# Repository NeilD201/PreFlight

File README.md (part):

# PCB Preflight — circuit review and manufacturing handoff

_Preflight was completely built during the hackathon — none of it was started before the hackathon kickoff._

> 🎬 **Hackathon demo video:** _link coming soon — placeholder for the recorded
> walkthrough (wrong board → findings → SRV05-4 prescription → disposable fix)._

Read a KiCad project folder or ZIP, compare schematic and PCB components and
connections, run KiCad's electrical and board rule checks, explain their practical
significance, and optionally ask AI to review the structured evidence. Requires
Python 3.10 or newer. The local checks use the standard library; PDF reading uses pypdf.
KiCad 9+ supplies the optional netlist/ERC/DRC engine (tested with KiCad 9.0.5).
See [project structure and data flow](docs/PROJECT_STRUCTURE.md) for a source
map, outbound service list, and local-data notes before publishing or sharing.
Two bundled demo boards (`demo-projects/ModularKeyboard wrong` and
`demo-projects/ModularKeyboard correct`) open with one click from the Projects
page — no upload needed. Both boards are the developer's WenneBoard project:
[wrong-board context](demo-projects/ModularKeyboard%20wrong/preset-context.md)
and [correct-board context](demo-projects/ModularKeyboard%20correct/preset-context.md)
(full text in [DEMO_GUIDE.md](DEMO_GUIDE.md)). After opening a demo and
running an analysis, load it via **Project context → Load preset → Save
context** so Vector can use the detailed WenneBoard information in
future reviews.

## Quick Start for Judges (under two minutes)

1. **Install:** Python 3.10+ (python.org, or `py -3` on Windows), then in the
   cloned folder create and activate a venv (exact PowerShell vs Command
   Prompt commands in SETUP.md §3), then `pip install -r requirements.txt`.
   Optional but recommended: KiCad 9+ (kicad.org) for native ERC/DRC and
   manufacturing checks — without it those checks report NOT PERFORMED
   instead of guessing.
2. **Launch:** `python main.py --web` and open the printed URL.
3. **API key (only needed for AI answers):** get a Meta API key with Muse
   Spark 1.3 Contributor access, then paste it in **Vector settings → Save &
   test**, or put `LLAMA_API_KEY=your-key` in an untracked `.env` file
   (see `.env.example`). Without a key, all local checks, findings, and
   previews still work; AI review and Vector answers report unavailable.
4. **Demo:** open **ModularKeyboard Wrong**, press **Check my board**, inspect
   the C105 capacitor and LED-resistor findings (USB-C CC detail and Vector
   follow-ups need the key), then open **ModularKeyboard Correct** to
   compare. See the full walkthrough below.

## What PreFlight is (and is not)

PreFlight reviews an **existing PCB design before manufacturing**: it reads your
KiCad schematic and PCB, checks that they agree, runs the electrical and
manufacturing rules that matter for a working board, and explains each finding
with evidence you can inspect. It was built because raw DRC output tells you
*what* violates a rule but not *whether it matters* — and because generic AI
chat answers printed-circuit questions without ever reading the design files.

PreFlight is **not an AI PCB generator** and does not lay out boards. Deterministic
checks (parsing, connectivity, ERC/DRC, manufacturing rules) always run locally
and are free. Meta Muse Spark is used only as a reasoning assistant over that
evidence — citations required, nothing accepted on a model's word alone.

## Judge walkthrough (about 10 minutes, no API key needed for steps 1–5)

1. Install and launch: `python3 -m venv .venv && source .venv/bin/activate`
   (Windows: `py -3 -m venv .venv`), `pip install -r requirements.txt`,
   then `python main.py --web` and open the printed URL.
2. On the Projects page, open **ModularKeyboard Wrong** (display name for the
   bundled `ModularKeyboard wrong` demo). It opens as a disposable working
   copy — the bundled originals are never modified.
3. Press **Check my board**. The local analysis runs on your machine (tens of
   seconds) with no API key.
4. Open **R001 — 100 µF capacitor (C105)**: rails (+5V, +3.3V), regulators,
   and every powered load pin, with steps naming exactly what is unverified.
   Open **R005 — LED series resistance (R12–R14)** for the screening
   estimate. (The USB-C CC pull-down detail appears with a Meta key's
   Vector review, not in the free local pass.)
5. Open a finding: schematic/PCB evidence, the pins and nets involved, and
   what would need to change. With a Meta key configured, ask Vector a
   follow-up (e.g. why the value matters); without a key this step reports
   itself as unavailable instead of guessing.
6. Open **ModularKeyboard Correct** and compare: the same checks pass there.
7. Explore the other findings (regulator pads, copper clearance, ESD
   protection) and the board preview, schematic view, and manufacturing
   checks.

A full AI review of a 400+-part board takes several minutes and a few cents of
Meta credit; nothing in the walkthrough above requires it.

## Reading a verdict: PASS, FAIL, NOT VERIFIED, NOT PERFORMED

- **Supported / fixed:** a deterministic check ran and the evidence meets the
  requirement, or a repair was applied to a disposable copy and re-verified.
- **FAIL / finding:** a check ran and the evidence contradicts the requirement.
  Each finding cites components, nets, pins, and source evidence.
- **NOT VERIFIED:** the evidence is incomplete, contradictory, or needs a
  measurement, simulation, or answer only you can give. Nothing is declared
  safe on missing evidence.
- **NOT PERFORMED / unavailable:** a check could not run (for example KiCad or
  datasheet PDFs are missing, or no Meta key is configured). The report says
  so instead of passing silently.

PreFlight never invents a specification, never treats an AI opinion as proof
on its own, and never edits your original KiCad files — repairs apply to
disposable copies only.

## Keep AI usage low

For a model-directed engineering investigation, choose **Vector settings → Vector
usage → Vector investigation · detailed review**. Vector selects evidence tools,
reviews their results, retrieves additional passages for open questions, and
challenges its circuit conclusions. The saved review includes an expandable
execution record. It shares the existing 12-request allowance. See [Vector
pipeline](docs/VECTOR_PIPELINE.md) for capabilities,
repair validation, and limits.

If a saved review has an AI failure, use **Retry AI review** on Overview or in
**More tools → Review log**. This reviews the saved board with the latest saved
product context. It reuses local checks, datasheets, assembly results and previews;
it does not rerun KiCad or look up the same parts again. Changed linked KiCad files
require **Update review** first. Repeated clicks do not start duplicate requests.
The result is saved as a new review, preserving the previous report.

**Save & test** sends one small structured request, with no PCB data. A successful
connection test establishes that the selected key and model answered that test;
the board review still needs to complete. Request limits do not replace the
provider's actual error, and incomplete responses never become accepted edits.

After reading the project, **Tell PreFlight about your project** invites one free-text
description of what you are building (up to 6,000 characters, saved with **Save &
analyse**). The description enters the engineering evidence and the optional Vector
review; it can be edited later. **Questions from your files** then asks only about
missing external facts identified from components and pin/net connections. For example, a charger
prompts for its attached battery, and a radio prompts for its final enclosure.
Each question shows what the files already establish. Questions are generated
locally for recognized circuit patterns, with no AI requests; they do not cover
every possible missing requirement. The AI review waits for these answers.
Choose **Not sure yet** when needed. **Product details** lets you revise answers.
Every **Continue** saves the answer immediately to `reports/.preflight.sqlite3`,
including **Not sure yet**. Closing the questionnaire or failing an AI request
does not discard submitted answers. Only unanswered questions are queued; completed
interviews open their saved-answer summary. Product-use answers survive board edits;
component-specific answers require reconfirmation when their electrical basis changes.
Reviews, chat and repair planning receive the question text alongside
these assumptions and related edge cases. Unknowns do not become passed checks.
Closing the questions preserves local results and leaves the AI review pending.
**Questions & saved answers** also lets you save AI follow-up answers without
starting a paid review. Repair answers are saved before the next investigation.
Context revisions are journaled in SQLite, and stale writes from another tab are
rejected rather than overwriting newer answers.

PreFlight uses one complete-investigation tier: there is no economy mode.
A Vector review uses up to 12 provider requests, including evidence-tool
investigations, per-finding verification, and a bounded repair loop. Repair
actions have their own per-action request cap; chat answers have a 2-request
cap. Each click that starts a new action gets a new allowance. These are
request limits, **not a euro spending cap**; token usage depends on the
project and response length. Local validation still runs, and unresolved
checks or unsafe edits are not accepted to fit any allowance.

Identical, fully validated reviews are reused in memory for up to 30 minutes
(eight entries maximum). Changed evidence, source hashes, context, model or
credentials require a fresh review. Partial or failed reviews are not reused.
Opening the app and saving settings do not test the API. **Save & test** sends
one small paid request. The AI review panel shows requests sent for new reviews.

## Start the browser app

From the project folder (whatever it is named), run:

```sh
python3 launch_app.py
```

This opens **http://127.0.0.1:8765** and keeps the app running in the background.
You can close the launch window. Double-click **Start PCB Preflight.command** in
the project folder to start it again; if it is already running, this reopens it.
Startup details are saved in `reports/.webserver.log`. For a foreground server
that stops with Ctrl+C, use `python3 main.py --web`.
Connect the `.kicad_pro`, `.kicad_sch` and `.kicad_pcb` files you edit in KiCad.
Save in KiCad, then click **Update** to read the saved files again. You can also
use **Upload ZIP** to check a KiCad archive (up to 100 MiB).

**Overview** lists active issues first, with **View issue**, **Fix this issue**, and
**Ask about it**. **Chat** beside **Review** is a general conversation: ask anything,
with no required issue or step. It uses a compact snapshot of the open project and
relevant saved evidence automatically, and also works without a project. Opening it
sends no AI request. Each message uses the existing two-request chat allowance, without
rerunning the review. Project conversations are stored in SQLite and restored across
updates and restarts. **Clear chat view** clears the visible conversation while
keeping saved history. The latest 100 exchanges are visible; the full archive remains
in the database. Up to 20 recent user messages with their preceding prompts, bounded
to 12 KB, are supplied as conversational context. Explicit product and follow-up
answers are supplied separately. Assistant suggestions are not saved as verified facts.
Chats without an open project remain session-only. Issue-specific
help remains available inside each issue. The repair
workflow prepares and checks proposed changes before approval; the button does not
mean every finding has an automatic edit. The manufacturing checklist follows. It separates
completed checks, findings to review and unverified engineering requirements.
It covers connections, power, PCB geometry, signals, mechanical fit, parts,
test access and production files. Expand a section for its evidence and next action.

New full runs refill copper on a temporary copy using KiCad Python, run DRC and
schematic parity, then export Gerber and Excellon drill drafts from that same copy.
The app validates layer attributes (including renamed copper layers), includes
source and output SHA-256 hashes, and offers the checked PCB copy for inspection.
Analysis leaves the original project unchanged. Missing KiCad Python, invalid outlines and
export failures remain visible; they never produce a fabricated success result.

### Optional file fixes

Each finding has **Fix this issue** above **Observation**, beside the design preview.
The details follow **Observation → Action → Consequence**, with supporting analysis below.
The button opens the available fix options for that finding.
For supported edits, save and close that board’s PCB Editor window,
tick the confirmation, then click **Apply fix**. The project manager and schematic can stay open. The app
prepares a copy, validates the edit, keeps a backup, and applies it automatically
if the checks pass. It currently supports copying one mismatched PCB Value field
from its matching schematic symbol, and short ground connections (up to 1.5 mm)
between an identified pad and a straight track on the same copper layer/net.
For other findings, **Fix this issue** starts an investigation in that same window when Meta is connected.
Progress, the repair assessment, retries and follow-up questions stay there. Closing and reopening
the window during the same page session keeps the investigation; it does not send it again.
Investigation requests retry transient server/connection failures up to three attempts, with
a 45-second socket timeout per attempt and a shared 120-second retry budget. Authentication,
quota, certificate and permanent DNS failures are reported without automatic retries.
The investigation asks Meta Muse Spark to assess whether a change
is needed using the selected path, connected parts, stored design context and available
datasheet excerpts. KiCad can stay open during this assessment. Chat proposes changes;
it cannot write files. Other edits remain manual.

Copper proposals must remove the exact unconnected-items finding after a KiCad
refill and DRC comparison without introducing new non-excluded DRC findings.
These checks use the saved rules and do not validate return-current behavior or EMI.
Keep the PCB Editor closed while the fix runs. The app checks source hashes again, keeps an original
backup, and replaces only the selected PCB file. Reopen the PCB in KiCad and
update the review using the button in the completion message. **Undo this fix** restores the original only if no subsequent
PCB edits would be overwritten. Previews and backups are in `reports/.file-fixes/`.
Edits require a connected local folder; uploaded files and ZIPs are copies.

The checklist also exposes ignored rules and saved exceptions. Symbol pin names
can identify I²C lines even when nets have arbitrary names; fitted pull-ups are
traced to recognized supplies and parallel resistance is calculated. Supply
voltages, bus timing, addresses and alternate pin functions still require evidence.
See [the manufacturing check coverage](docs/PREMANUFACTURING.md) for scope.

The top menu has three review sections:

- **Circuit**: supported circuit concerns from pin requirements, datasheet passages,
  functional paths and operating context. Raw ERC does not become a connection mistake
  on its own. Pin analysis can raise a wiring correction or a specific missing-mode question.
- **PCB layout**: spacing, holes, mask, footprints and assembly checks. These use
  saved KiCad rules; they are not a complete datasheet placement or manufacturing review.
- **Signals**: shorts/unconnected items, circuit paths, radio/sensor routing
  observations, saved stackup, and limited DC trace estimates.

**KiCad & library notes** retains raw ERC, naming, library and unavailable-check notices.
Each section shows a marked preview beside the selected finding, its possible impact
and the next step. Additional steps, analysis and source evidence expand on demand.
The question box stays open for the selected finding; **Ask a question** at the top
jumps to it. You can ask about a footprint note as well as an active issue.
Default-clearance warnings between known pads in the same footprint, and shared mask
openings inside that footprint, are kept in **KiCad & library notes**. They do not
generate pad-moving instructions. This classification does not approve a land pattern
or manufacturing process: shorts, zero gaps, unknown pad ownership, routed tracks and
explicit clearance rules are not suppressed. Old saved AI steps are also corrected
when viewed, without marking these findings fixed or rewriting historical reports.
**Project → Edit intended use & operating details** provides interfaces, power, antenna
and manufacturing fields used together by the AI. Connected files and check settings
also live under **Project**. Empty sections do not certify the design. **More** retains
datasheets, original findings, AI status and the net browser; **BOM & parts** holds exports.

The DC model uses the saved copper thickness and TI's nominal 25 °C resistivity formula.
Only a connected, unbranched, single-layer chain of straight tracks is estimated. Nets
with vias, pours, arcs, branches, loops or intersections remain uncalculated. The estimate
is between drawn track endpoints, not component pins: pads, contacts, parts and heating
are excluded. It is not RF impedance. No return-plane, noise, crosstalk, antenna or thermal
simulation has run, and no acceptable voltage-drop/current limit is inferred.

**Projects** has searchable,
paginated history, including reports previously generated from Terminal. Give each
board a project name and reuse it for later revisions. The last opened run is restored
when the app restarts. Checks use temporary copies of the KiCad files.

### Follow the circuit

**Circuit / Signals → Explore circuit paths** traces the saved schematic connections through
supported charger and regulator stages, fitted series parts, and receiving pins.
Choose a circuit path and, where available, its source route. Click a pin to mark its
saved schematic position, or show the complete path and switch to **PCB** to highlight
its drawn copper. Signal paths also show the shared bus endpoints and side branches.

The smartwatch example includes J1 → U8 → U4, J4 → U4, U4 → U12,
the SCL/SDA sensor buses, and U13 → L1 with the antenna capacitor branches.
The AI review and step helper receive these traced paths alongside pins and datasheet
passages. Unknown internal IC connections and switch states are left unresolved.
A path through a regulator describes its intended function; it does not mean its input
and output share copper. Shunt capacitors are kept separate from DC power paths.
The highlights show saved routing, without calculating noise or impedance.

### Describe the device, then revise the change plan

**Project → What the app understands** describes the device inferred from the selected components.
Without AI this is labelled as an initial interpretation from component names. With
Meta Muse Spark it is reconsidered against the circuit evidence and your stated intent.

1. Correct the description or add constraints: power source, operating modes, external
   circuitry, interfaces, intended measurements and manufacturing requirements.
2. Select **Save & review**. This saves context and creates a new report using
   the same circuit evidence, without rerunning KiCad. A configured Meta key enables
   the AI review; without one, local steps remain available and are labelled accordingly.
3. Each item has ordered change/investigation steps. Use **Is this intentional?** to
   explain an exception, then **Use this context & rethink**. The AI must address the
   explanation and can revise the steps or retain the issue with a reason.
4. Context persists for the named project and root schematic. Notes on findings and
   selected part identities must be reconfirmed when their underlying evidence changes.
   Old reports retain the context snapshot used for their review.

Intent is not proof of a fix. Original findings are preserved. Failed AI requests keep
the saved context and local steps, and report that reconsideration did not complete.

### LCSC datasheets

Install the optional PDF reader in this project:

```sh
python3 -m pip install --target .deps -r requirements.txt
```

Each browser run automatically searches LCSC for fitted components and reads the PDF
linked to each chosen product. Explicit codes and exact MPN matches are assigned directly.
Family names and passive values/packages receive **automatic candidate** selections,
already included in the draft BOM. Candidate choices remain provisional until reviewed.
Generic labels such as `LED`, or crystals without a frequency, remain unresolved.

The matcher compares passive values and imperial package sizes, filters recognized IC
package and pin-count conflicts, and excludes development boards from chip searches.
It does not establish pinout, rating, dielectric, substitute or assembler compatibility.
Open **Parts & datasheets** to inspect the selection and its PDF, confirm a group of
identical parts or replace it with an exact LCSC code. This regenerates the BOM and plan.

Downloads use an HTTPS host allowlist, size/time limits and a seven-day local PDF cache
in `reports/.datasheets`; search results are cached for one day. Lookups share repeated
value/package queries and prioritize ICs, with an 80-query / four-minute budget. A run
can finish an in-progress bounded request after that budget. Deferred items remain visible;
rerunning uses the cached results. Stock is a search-time snapshot, not an order reservation.

PDF text is extracted in a bounded subprocess (up to 80 pages / 500,000 characters).
The initial warning review receives three passages per part, or six for flagged pins.
An independent functional review then examines active parts even when ERC reports no issue.
It retrieves up to twelve passages per part across pin functions, operating limits,
interfaces, startup, supporting components and signal requirements. Each small request
includes neighboring pins, component values and traced circuit paths. A second request
audits both proposed corrections and claims that a connection is consistent.

Open **Circuit → Circuit analysis** to see these comparisons and their missing facts.
Supported concerns appear in the normal issue list with exact pin markers. Unknown
requirements remain open questions rather than suggested wire edits. The review uses
the configured model with high reasoning effort for these focused requests. It makes
more API requests than the warning review and can use more of your provider quota.
Limits: eighteen active parts per run, eighty seconds per request, and six minutes for
the functional stage. Unreviewed parts and failed requests remain listed explicitly;
completed comparisons are preserved. A short rate-limit delay is retried only when
the provider supplies a reset within sixty seconds, with at most two pauses per run.
The initial warning stage has its own time limit.
Automatic candidates are labelled provisional and may only support investigation steps.
Page IDs and short quotations are validated against the supplied text. Scans, inaccessible
files and incomplete text are reported; a readable PDF is not required to keep a retrieved
part identity in the BOM. Quotation validation does not establish that the conclusion
follows from the quote, or that omitted diagrams/tables contain no further requirements.

Lookup sends part names/codes to LCSC. Meta Muse Spark receives structured circuit evidence,
your context and selected PDF excerpts. API keys stay in server memory during use. With **Remember key on this Mac**, the app also stores the key in macOS Keychain and restores it after restart. Downloads
and the change plan work independently of KiCad analysis; board files are not edited.

### Automatic BOM and CPL downloads

**BOM & placement files** appears below the device description after each run:

- **Download BOM + CPL**: ZIP containing the files below and a checksum manifest.
- **bom-draft.csv**: grouped `Comment,Designator,Footprint,LCSC Part #` rows for fitted
  PCB components. Equivalent passive values group together. Unresolved codes stay blank.
- **cpl-draft.csv**: `Designator,Mid X,Mid Y,Layer,Rotation`, generated by KiCad CLI
  from the exact PCB bytes used for the report. Coordinates are in mm, using KiCad's
  drill/place origin, with both sides and native rotations. No assembler-specific rotation
  correction is guessed. Check the assembler's preview before ordering.
- **sourcing-review.csv**: every part's selected MPN/code, match basis, review notes,
  listed specifications, stock snapshot, source links and placement status.

DNP, excluded-from-BOM and mechanical components are omitted. A footprint excluded
from position files stays in the BOM and is labelled accordingly in the worksheet.
Duplicate or case-colliding references block BOM/CPL output. Without KiCad, the BOM
still downloads and the missing CPL is explained. Saved placement snapshots support
context/part updates after an uploaded ZIP has been removed or the app restarted.
Changed source bytes require a new check before a fresh placement snapshot can be made.

The command-line checker does the same sourcing and exports. Use `--no-sourcing` to
skip online lookups. In the browser, uncheck automatic LCSC lookup for an offline run.
CPL files contain placements; the BOM contains their LCSC part numbers.

### Other review tools

- **Before you order** shows available evidence, missing checks and next actions.
- **Check evidence** lets you record Open, Reviewed or Accepted risk with a reason.
  Notes persist across restarts, include a change history, and apply only to that run.
  These decisions preserve the original findings. A decision is not a verified fix.
- **BOM & placement** compares BOM/placement CSVs with the PCB and shows declared
  part numbers, missing identities and conflicting MPNs. It does not verify live stock,
  pricing, substitutes, electrical ratings or the supplier package pinout. Generated
  LCSC assignments are shown alongside the imported evidence.
- **Compare runs** compares finding groups, component values/footprints/positions and
  schematic net membership against a baseline from the same project (latest 100 runs).
  A drop in check coverage is called out before interpreting absent findings.
- **Export review package** downloads a ZIP with the report, decision journal, parts
  and findings review worksheets, generated assembly drafts, and SHA-256 checksums.

### BOM and placement checks

Include UTF-8 CSV files in the project folder or ZIP. Supported separators are comma,
semicolon and tab. Recognized headers include KiCad's `Ref,PosX,PosY,Rot,Side` and
`Designator,Mid X,Mid Y,Layer,Rotation`, plus common BOM field aliases.
References like `C1, C2, C3-C5` are expanded; each placement row must name one part.
Use **Assembly files & coordinate units** when multiple candidate CSVs exist.

Checks cover duplicate/invalid references, quantities, missing/invalid coordinates,
rotation and layer, reference mismatches, DNP conflicts, side mismatches and clear
passive-package mismatches. Descriptive BOM value differences remain review items.
Mechanical/DNP exclusions and through-hole or placement-excluded footprints receive
different treatment from expected automated placements.

Bare coordinates have **unknown units** until you confirm mm or inches. Unit-bearing
headers/cells are recognized; contradictory units are rejected. Position origin,
mirroring, rotation conventions, physical centroid accuracy and assembly variants
remain unverified. CSV validation does not imply placement geometry is correct.

Format references: [JLCPCB BOM](https://jlcpcb.com/help/article/bill-of-materials-for-pcb-assembly),
[JLCPCB placement](https://jlcpcb.com/help/article/pick-place-file-for-pcb-assembly),
and [KiCad 9 position export](https://docs.kicad.org/9.0/en/cli/cli.html#pcb-position-file-export).

```sh
python3 main.py /path/to/project --bom exports/bom.csv --cpl exports/positions.csv --cpl-units mm
```

### Storage and operating limits

`reports/.preflight.sqlite3` stores the indexed project history, review decisions and
preferences. Each completed report remains an independent folder. Back up the entire
`reports/` directory while the app is stopped, including the database. Keep notes with
the reports they refer to. New reports are published only after every file is written;
failed saves do not leave a partial report in the library. Inputs receive SHA-256
fingerprints, and a source edit during a run makes that run fail instead of mixing revisions.

Listings use indexed metadata and pagination. Large component, raw-finding and parts
lists render 100 rows at a time. Refresh the library to discover CLI reports created
while the server is open. KiCad jobs remain sequential because this local engine uses
application-level resources. This release is one trusted local workspace, with no
customer accounts or hosted multi-user isolation. See [PRODUCT.md](PRODUCT.md) for
the remaining product work.

In **Vector settings**, paste a Meta API key and choose **Save & test**.
PreFlight uses Meta Muse Spark 1.3 Contributor exclusively — there is no
provider selector and no automatic fallback to another model. The existing
evidence validation and staged KiCad checks still apply.

**Remember the key on this Mac** stores it in macOS Keychain. The key never
enters reports or browser storage. The server also accepts `LLAMA_API_KEY`
as an environment variable, or from an untracked `.env` / `.env.local` file
(see `.env.example`). **Include AI review** sends structured evidence to the
Meta API; leave it unchecked for local-only checks. Selecting Save & test
sends one small request; selecting a model alone does not establish access.

The app listens only on this computer. Uploaded ZIPs are held in a temporary folder
until the server stops; completed reports remain in `reports/`. One check runs at a
time. Stop with Ctrl+C (an active check finishes before cleanup).

Useful launch options:

```sh
python3 main.py --web --port 8766       # If the default port is occupied
python3 main.py --web --no-browser     # Start without opening a browser
python3 main.py --web --no-ai          # Start with AI review unchecked
python3 main.py --web /path/to/project # Prefill another project
```

## Start the command-line checker

Open Terminal and run from the project folder:

```sh
python3 main.py
```

When it asks for the unzipped folder name, enter a folder inside the checker
directory, or a full path. If a project was previously connected, the prompt
offers it as the default; press Enter to use it. To change the default
without editing the code, set `PCB_CHECKER_PROJECT` to another folder or ZIP.

To skip the prompt, pass a folder or ZIP directly:

```sh
python3 main.py /path/to/your-board
python3 main.py /path/to/project.zip
python3 main.py /path/to/project.zip --json
```

`--json` includes every parsed component, both source records, original
properties, file paths, and source line numbers. The prompt goes to stderr,
so stdout remains valid JSON. Imports and checks do not modify the KiCad files.

If the checkout folder itself is named `pcb_checker`, `python3 -m pcb_checker` also works from its parent directory.

## Reports and component inspection

The default report leads with **Check evidence**: concrete discrepancies,
fabrication constraints, assembly concerns, and schematic/library setup. Cosmetic
findings are available under the Show menu. A via flagged by three rules appears
as one physical item in a grouped explanation. Original severities and every
underlying finding remain accessible under **Raw findings** and in JSON.

Each group explains the evidence, what could go wrong, what remains uncertain,
and a next step. These explanations are local rules; they are not labelled as AI.

The **Circuit context** tab lists supply-to-ground capacitor connections and
external pull-up resistors on SDA/SCL candidates. It does not assume every IC
needs a generic capacitor or infer voltage ratings from rail names. Component
details also show existing MPN, manufacturer and LCSC fields when present.

Two narrow manufacturer rules run when connectivity is available:

- MCP73831 DFN: compare exposed pad 9 with VSS pad 6; report nominal charge
  current when one supported programming resistor can be identified.
- MAX30102: distinguish its six documented NC pads from missing electrical
  connections; flag assigned nets or missing package pads for review.

Rules match declared part identities, not `U8`/`U11` reference names. Sources and
page/section information are included. The browser's separate LCSC lookup can retrieve
other matched datasheets; the fixed local rules do not expand automatically from PDF text.

A normal run automatically detects KiCad on PATH or in its standard macOS
installation, performs the checks, and prints the saved report path. Open
`report.html` in your browser. The report has severity and text filters,
expandable findings with evidence, component pin tables, and searchable net members.

Every run gets a new folder under `reports/` in the project folder. Earlier reports are
preserved. Each contains `report.html`, `report.json`, and the successful native
`kicad-erc.json` / `kicad-drc.json` reports. Local checks upload nothing. Optional
AI behavior is described below.

```sh
# Inspect a component's schematic and PCB connections in the terminal:
python3 main.py /path/to/project --component U13

# Ask deterministic connectivity questions without AI:
python3 main.py /path/to/project --pin U8.8 --no-ai
python3 main.py /path/to/project --net SDA --no-ai

# Show the old detailed terminal output:
python3 main.py /path/to/project --raw

# Select a KiCad executable or a report destination:
python3 main.py /path/to/project --kicad-cli /path/to/kicad-cli --output-dir /path/to/reports

# Use only the built-in component checker:
python3 main.py /path/to/project --skip-kicad

# Print machine-readable results without saving files:
python3 main.py /path/to/project --json --no-save
```

If KiCad is unavailable or a command fails, the report explicitly says which
checks could not run. A missing result is never treated as a passed check.

## AI review and questions

### Meta Muse Spark setup (paid)

PreFlight's AI review uses Meta Muse Spark 1.3 Contributor and nothing else.
There is no free tier: every AI review, question answer, and repair assessment
is billed to your Meta key at Contributor rates (currently $0.10 in / $0.002
cached / $0.20 out per 1M tokens — check Meta's current pricing). A full board
review typically costs a few cents; the top bar shows live spend and tokens.

1. Get a Meta API key with access to Muse Spark 1.3 Contributor.
2. Open **Vector settings** in the app, paste the key, and choose **Save & test**
   (one small structured request, no PCB data). Or, for Terminal runs, set
   `LLAMA_API_KEY` in your environment — or copy `.env.example` to an
   untracked `.env` file — and run `python3 main.py --test-ai`.
3. Tick **Include AI review** when starting a check. `--no-ai` keeps a run
   local. The local checks always finish even if AI is unavailable.

Avoid typing real keys into shell history or committing them. On macOS zsh,
this prompts without echoing:

```sh
read -rs 'LLAMA_API_KEY?Meta API key: '
export LLAMA_API_KEY
python3 main.py --ai-provider meta
```

Ask a focused question:

```sh
python3 main.py /path/to/project --ask "What could actually prevent this board from working?"
python3 main.py /path/to/project --ask "Explain the charger connections and the remaining uncertainties."
```

Meta uses structured JSON output with low thinking effort and bounded output
limits. Each API attempt can take up to three minutes, with at most three
attempts for transient server errors; quota and auth errors are reported
immediately with no silent provider switch.

### Diagnose an API failure

To test the key, model and structured response format without loading a project
or running KiCad:

```sh
python3 main.py --test-ai
```

This uses the same request builder and response validation as the PCB review,
with empty circuit data and a short test question. It makes one request, waits
up to 60 seconds, and does not retry or change models. It reuses the exported
key or prompts privately. The command saves no files. A successful small test
does not establish that a full board review will succeed.

Use `--ai-model MODEL` to test a specific model and `--json` for structured
diagnostics. On HTTP failure, Meta's error code and message are shown when
available. API keys and terminal controls are removed; only bounded JSON error
fields are read. The full review also saves these diagnostics in `ai-review.json`.
HTTP 503 alone does not establish that the key was accepted or identify why the
service failed. Repeated errors can represent one original request plus its
retry attempts.

The request contains normalized component identities, pin/net assignments,
grouped findings, circuit context and cited part rules. The full archive, arbitrary
custom properties and original absolute project directory are not sent. Requests
use `store: false`. Meta's API terms still apply. This setup is for your own
prototype testing; check Meta's terms before offering the app to other users.

PreFlight supports only Meta Muse Spark 1.3 Contributor. There is no
Gemini, OpenAI, or other-model option in the review path.

### Evidence and reliability

Each saved report includes:

- `ai-input.json`: the inspectable evidence packet.
- `ai-prompt.txt`: the review instructions and facts, usable manually in another AI tool.
- `ai-review.json`: model, completion status, evidence fingerprint, token usage and accepted response.

No API keys are included. Oversized evidence is rejected, rather than silently
omitted. Each AI observation must cite real evidence IDs; invalid citations,
malformed output, refusals and partial responses are rejected. AI interpretations
do not change deterministic findings. The browser review includes matched LCSC PDF
excerpts and saved intent. The CLI's original review uses the local circuit evidence.
Neither mode simulates the circuit, verifies live stock or automatically edits the design.

The HTML report shows **AI review has not run** when disabled, unconfigured,
cancelled or failed. It never substitutes a canned explanation for a model result.
Explicitly requested AI failures return exit code 3 after saving local results;
import/CLI errors use 2. Rule violations themselves do not change the exit code.

## Feature status: verified, partial, experimental

**Verified working** (test suites + real-board runs green):
- KiCad project parsing (schematic hierarchy, PCB footprints, nets, pads),
  schematic↔PCB comparison, deterministic electrical and manufacturing checks.
- Native KiCad ERC/DRC execution with timeouts and honest unavailable states.
- Meta Muse Spark investigation: catalog component discovery, datasheet
  excerpt retrieval with `D:` citations, per-finding verification,
  fix assessment, chat, and usage tracking.
- Exact-part prescriptions with quoted datasheet evidence (for example the
  USB-protection recommendation), conditional on unresolved user questions.
- Deterministic Fix Design for supported edits (value changes, verified
  ground connections): preparation stages disposable copies and re-verifies
  them; applying writes your linked project files with an automatic backup
  and undo.
- BOM/CPL drafts, fabrication exports, assembly manifests.
- Bundled demo boards, product-context wizard with bulk entry, report
  history, project persistence.

**Partially working / conditional:**
- Repair planning for non-deterministic edits needs a Meta key and may stay
  conditional when evidence is missing.
- The VBUS fuse recommendation stays conditional without supporting catalog
  evidence; the USB TVS recommendation is evidence-backed.
- Antenna/RF findings identify geometry and layout concerns but cannot prove
  RF performance without simulation or measurement.

**Experimental:**
- Firmware generation: nRF52 bare-metal C and RP2040 Pico SDK C (GPIO
  bring-up, I2C HAL, UF2 output) with 89 passing tests. No QMK, no
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
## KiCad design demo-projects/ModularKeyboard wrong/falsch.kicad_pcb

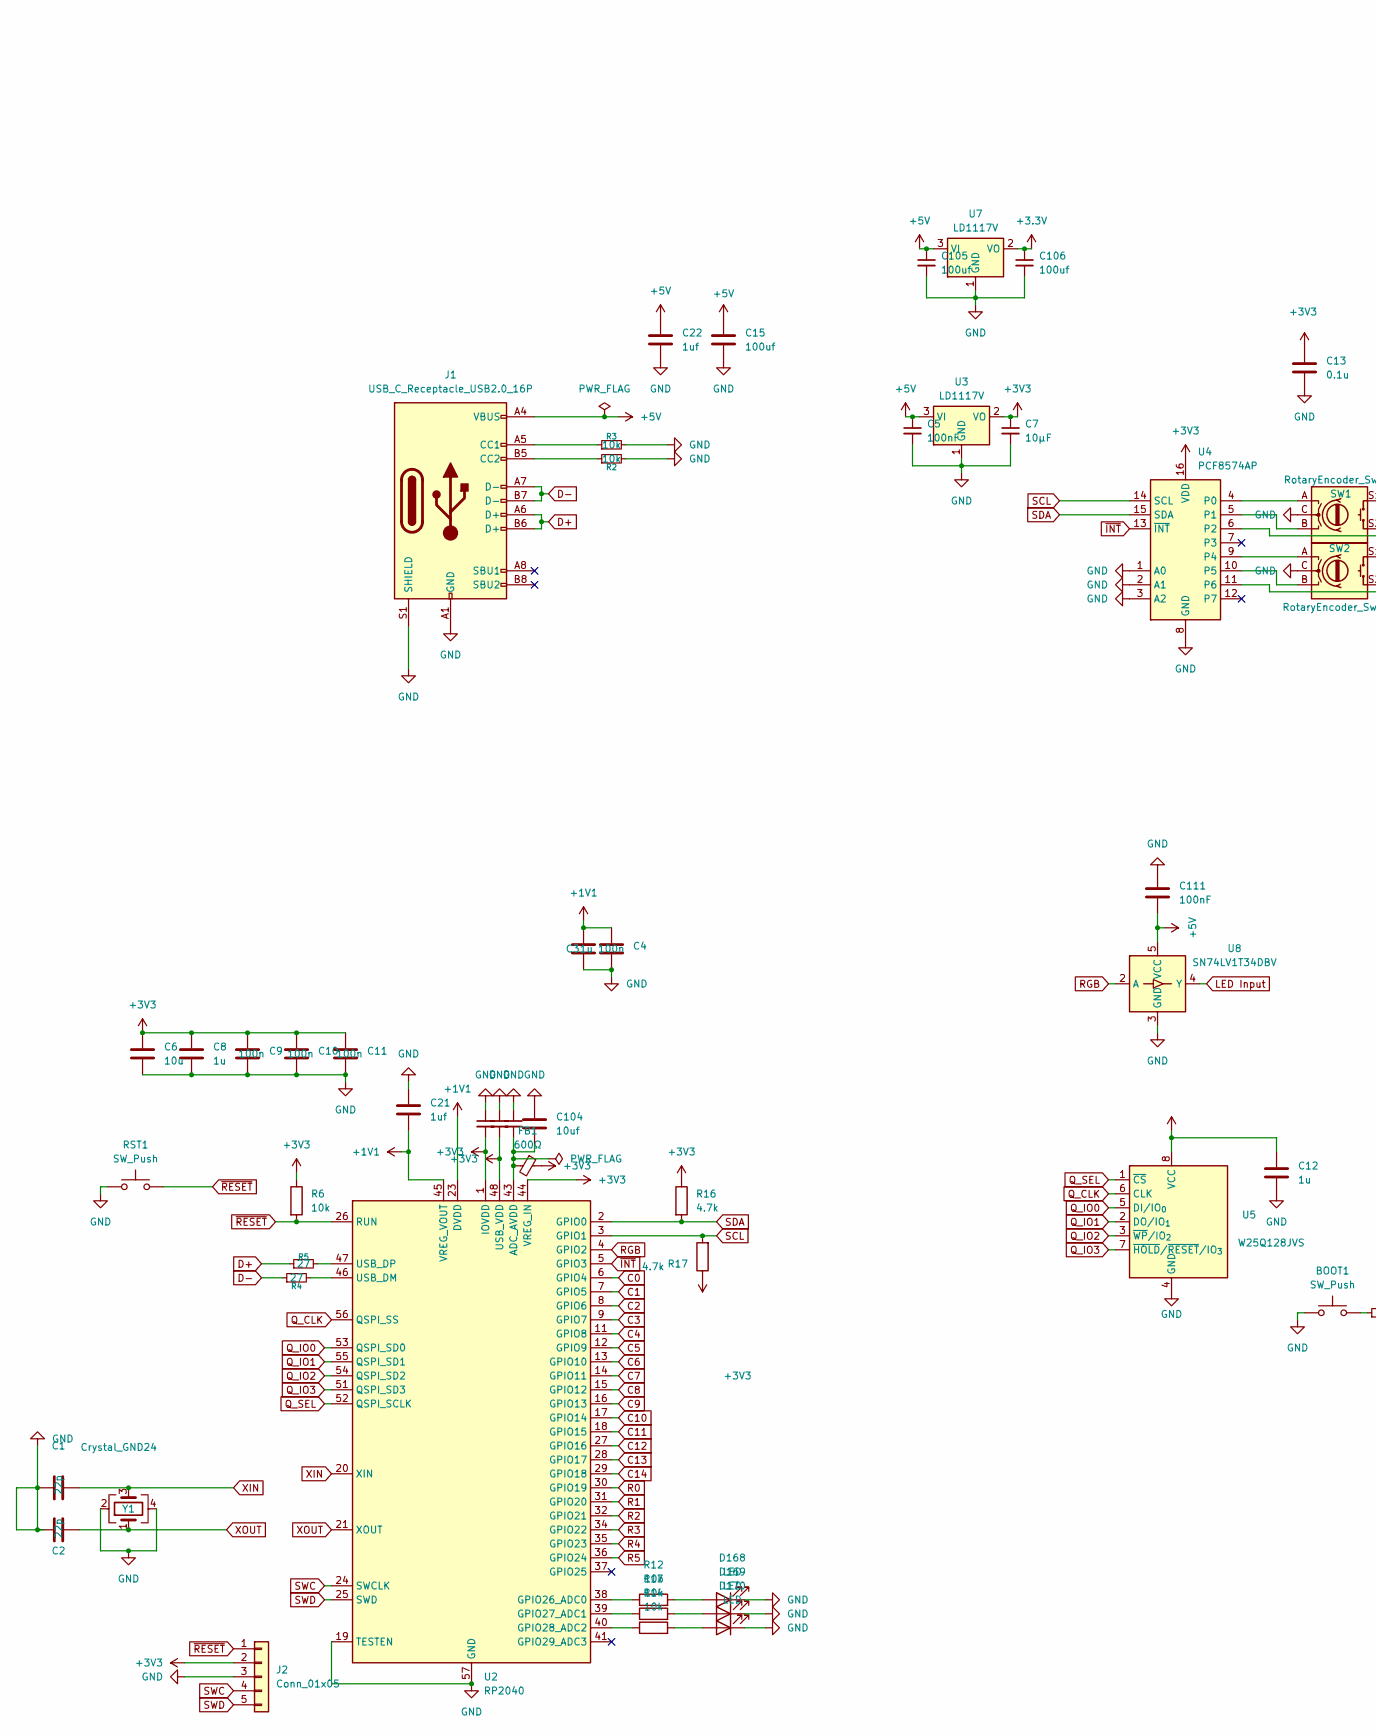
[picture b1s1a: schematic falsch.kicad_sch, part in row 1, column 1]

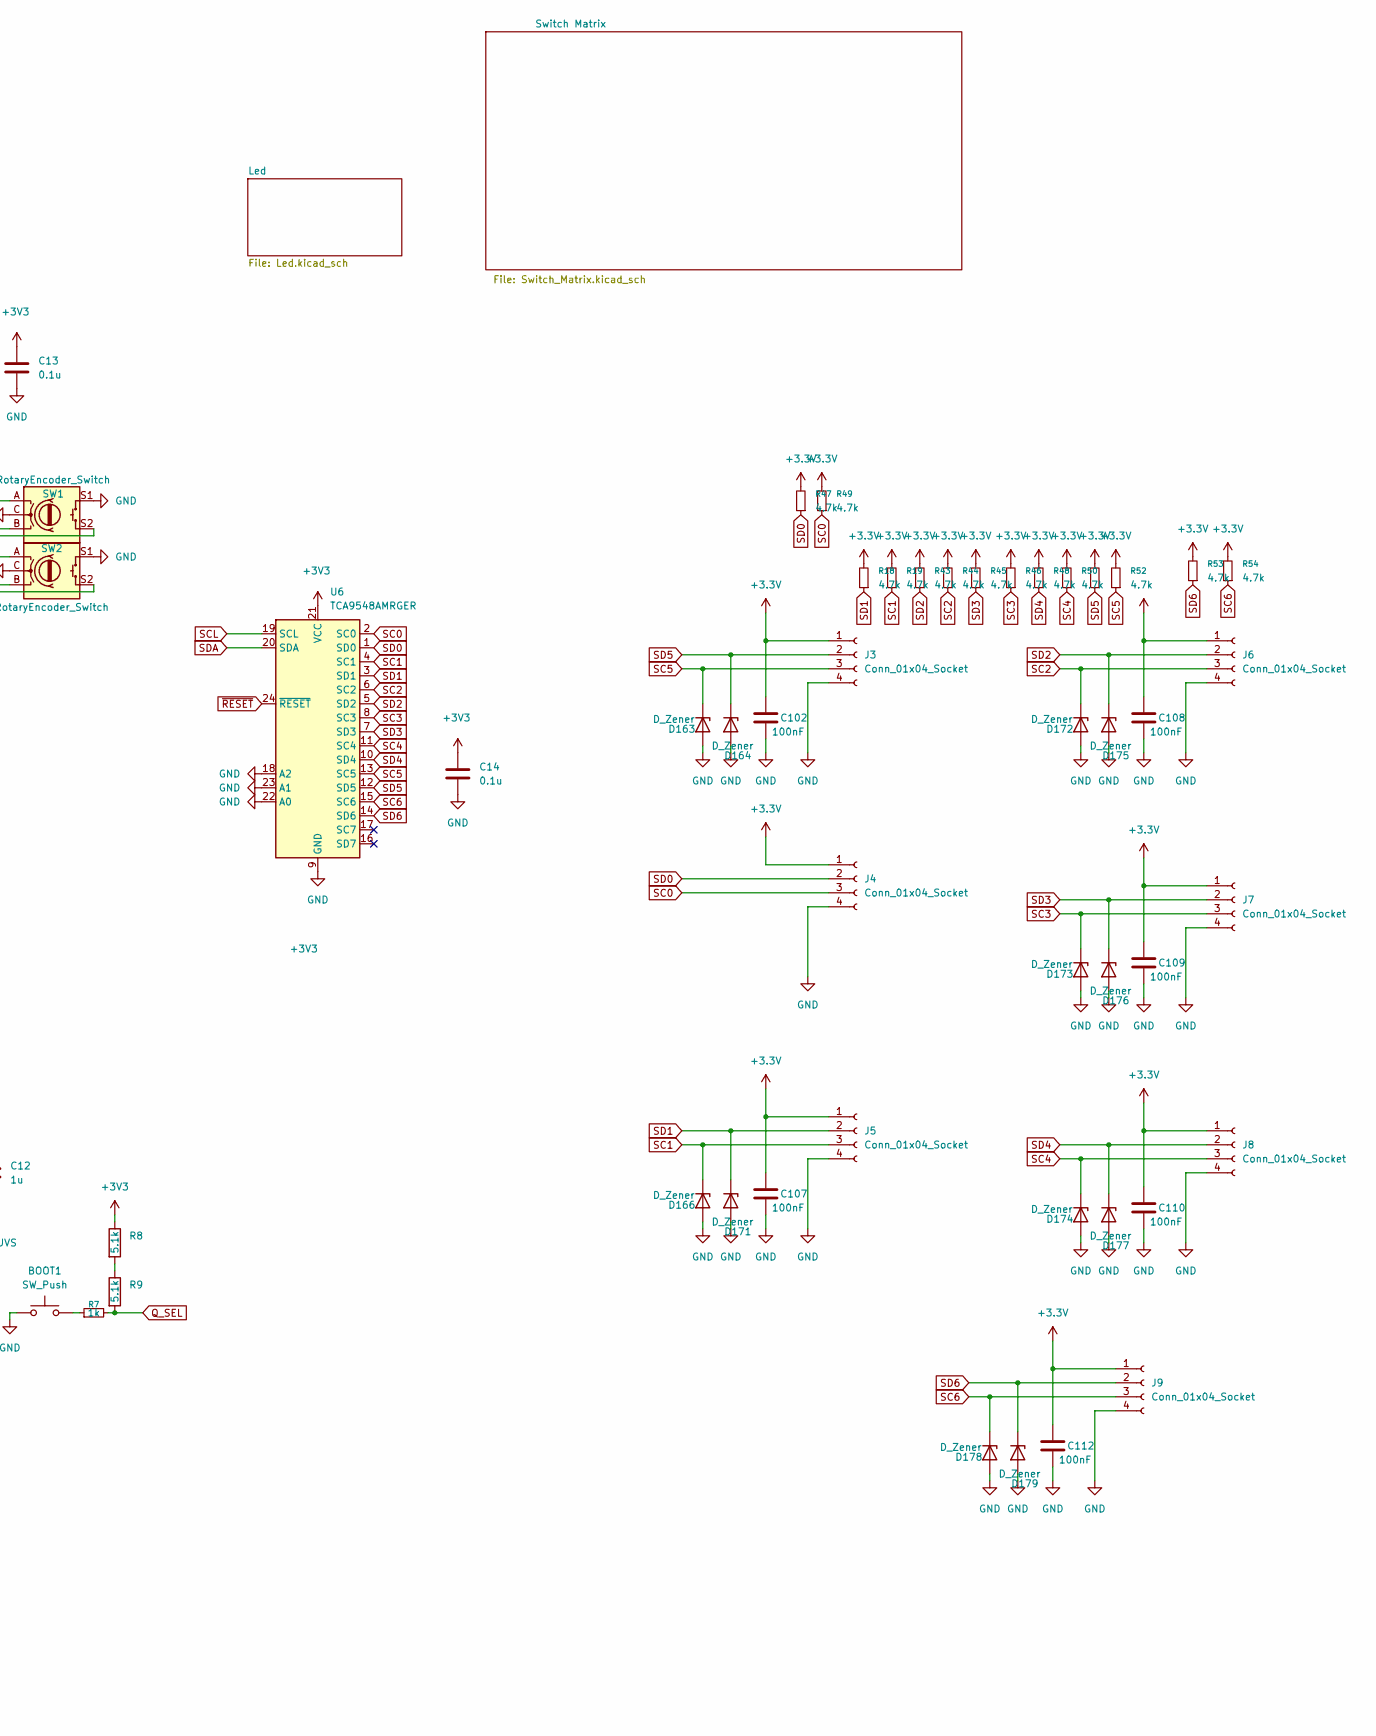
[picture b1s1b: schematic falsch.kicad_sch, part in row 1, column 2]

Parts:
BOOT1: SW_Push; SW_Push_1P1T_XKB_TS-1187A
C1, C2: 22p; C_0402_1005Metric
C3, C8, C12: 1u; C_0402_1005Metric
C4, C9, C10, C11: 100n; C_0402_1005Metric
C5, C102, C107, C108, C109, C110, C111, C112: 100nF; C_0402_1005Metric
C6: 10u; C_0402_1005Metric
C7: 10μF; C_0402_1005Metric
C13, C14: 0.1u; C_0402_1005Metric
C15: 100uf; CP_EIA-3528-21_Kemet-B
C18, C19, C20: 100nf; C_0402_1005Metric
C21, C22: 1uf; C_0402_1005Metric
C104: 10uf; C_0402_1005Metric
C105, C106: 100uf; C_0402_1005Metric
D163, D164, D166, D171, D172, D173, D174, D175, D176, D177, D178, D179: D_Zener; D_SOD-523
D168, D169, D170: LED; LED_0603_1608Metric
FB1: 600Ω; L_0402_1005Metric
J1: USB_C_Receptacle_USB2.0_16P; USB_C_Receptacle_HRO_TYPE-C-31-M-12
J2: Conn_01x05; PinHeader_1x05_P2.54mm_Vertical
J3, J4, J5, J6, J7, J8, J9: Conn_01x04_Socket; PinHeader_1x04_P2.54mm_Horizontal
R2, R3, R6, R12, R13, R14: 10k; R_0402_1005Metric
R4, R5: 27; R_0402_1005Metric
R7: 1k; R_0402_1005Metric
R8, R9: 5.1k; R_0402_1005Metric
R16, R17, R18, R19, R43, R44, R45, R46, R47, R48, R49, R50, R51, R52, R53, R54: 4.7k; R_0402_1005Metric
RST1: SW_Push; SW_Push_1P1T_XKB_TS-1187A
SW1, SW2: RotaryEncoder_Switch; RotaryEncoder_Alps_EC11E-Switch_Vertical_H20mm
U2: RP2040; QFN-56-1EP_7x7mm_P0.4mm_EP3.2x3.2mm
U3, U7: LD1117V; SOT-223
U4: PCF8574AP; DIP-16_W7.62mm
U5: W25Q128JVS; SOIC-8_5.3x5.3mm_P1.27mm
U6: TCA9548AMRGER; Texas_RGE0024C_VQFN-24-1EP_4x4mm_P0.5mm_EP2.1x2.1mm
U8: SN74LV1T34DBV; SOT-23-5
Y1: Crystal_GND24; Crystal_SMD_3225-4Pin_3.2x2.5mm

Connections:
+1V1: C3.1, C4.1, C21.2, U2.23 (DVDD), U2.45 (VREG_VOUT), U2.50 (DVDD)
+3.3V: C102.1, C106.1, C107.1, C108.1, C109.1, C110.1, C112.1, J3.1, J4.1, J5.1, J6.1, J7.1, J8.1, J9.1, R18.2, R19.2, R43.2, R44.2, R45.2, R46.2, R47.2, R48.2, R49.2, R50.2, R51.2, R52.2, R53.2, R54.2, U7.2 (VO)
+3V3: C6.1, C7.1, C8.1, C9.1, C10.1, C11.1, C12.1, C13.1, C14.1, C18.2, C19.2, FB1.1, J2.2, R6.1, R8.1, R16.1, R17.1, U2.1 (IOVDD), U2.10 (IOVDD), U2.22 (IOVDD), U2.33 (IOVDD), U2.42 (IOVDD), U2.44 (VREG_IN), U2.48 (USB_VDD), U2.49 (IOVDD), U3.2 (VO), U4.16 (VDD), U5.8 (VCC), U6.21 (VCC)
+5V: C5.1, C15.1, C22.1, C105.1, C111.2, J1.A4 (VBUS), J1.A9 (VBUS), J1.B4 (VBUS), J1.B9 (VBUS), U3.3 (VI), U7.3 (VI), U8.5 (VCC); also elsewhere on the board
C0: U2.6 (GPIO4); also elsewhere on the board
C1: U2.7 (GPIO5); also elsewhere on the board
C2: U2.8 (GPIO6); also elsewhere on the board
C3: U2.9 (GPIO7); also elsewhere on the board
C4: U2.11 (GPIO8); also elsewhere on the board
C5: U2.12 (GPIO9); also elsewhere on the board
C6: U2.13 (GPIO10); also elsewhere on the board
C7: U2.14 (GPIO11); also elsewhere on the board
C8: U2.15 (GPIO12); also elsewhere on the board
C9: U2.16 (GPIO13); also elsewhere on the board
C10: U2.17 (GPIO14); also elsewhere on the board
C11: U2.18 (GPIO15); also elsewhere on the board
C12: U2.27 (GPIO16); also elsewhere on the board
C13: U2.28 (GPIO17); also elsewhere on the board
C14: U2.29 (GPIO18); also elsewhere on the board
D+: J1.A6 (D+), J1.B6 (D+), R5.1
D-: J1.A7 (D-), J1.B7 (D-), R4.1
GND: BOOT1.1, C1.1, C2.1, C3.2, C4.2, C5.2, C6.2, C7.2, C8.2, C9.2, C10.2, C11.2, C12.2, C13.2, C14.2, C15.2, C18.1, C19.1, C20.1, C21.1, C22.2, C102.2, C104.1, C105.2, C106.2, C107.2, C108.2, C109.2, C110.2, C111.1, C112.2, D163.2 (A), D164.2 (A), D166.2 (A), D168.1 (K), D169.1 (K), D170.1 (K), D171.2 (A), D172.2 (A), D173.2 (A), D174.2 (A), D175.2 (A), D176.2 (A), D177.2 (A), D178.2 (A), D179.2 (A), J1.A1 (GND), J1.A12 (GND), J1.B1 (GND), J1.B12 (GND), J1.S1 (SHIELD), J2.3, J3.4, J4.4, J5.4, J6.4, J7.4, J8.4, J9.4, R2.2, R3.2, RST1.1, SW1.C, SW1.S1, SW2.C, SW2.S1, U2.19 (TESTEN), U2.57 (GND), U3.1 (GND), U4.1 (A0), U4.2 (A1), U4.3 (A2), U4.8 (GND), U5.4 (GND), U6.9 (GND), U6.18 (A2), U6.22 (A0), U6.23 (A1), U7.1 (GND), U8.3 (GND), Y1.2, Y1.4; also elsewhere on the board
LED Input: U8.4 (Y); also elsewhere on the board
unnamed: BOOT1.2, R7.1
unnamed: D168.2 (A), R12.2
unnamed: D169.2 (A), R13.2
unnamed: D170.2 (A), R14.2
unnamed: J1.A5 (CC1), R2.1
unnamed: J1.B5 (CC2), R3.1
unnamed: R8.2, R9.1
unnamed: C20.2, C104.2, FB1.2, U2.43 (ADC_AVDD)
unnamed: R12.1, U2.38 (GPIO26_ADC0)
unnamed: R13.1, U2.39 (GPIO27_ADC1)
unnamed: R14.1, U2.40 (GPIO28_ADC2)
unnamed: R4.2, U2.46 (USB_DM)
unnamed: R5.2, U2.47 (USB_DP)
unnamed: SW1.A, U4.4 (P0)
unnamed: SW1.B, U4.5 (P1)
unnamed: SW1.S2, U4.6 (P2)
unnamed: SW2.A, U4.9 (P4)
unnamed: SW2.B, U4.10 (P5)
unnamed: SW2.S2, U4.11 (P6)
Q_CLK: U2.56 (QSPI_SS), U5.6 (CLK)
Q_IO0: U2.53 (QSPI_SD0), U5.5 (DI/IO_{0})
Q_IO1: U2.55 (QSPI_SD1), U5.2 (DO/IO_{1})
Q_IO2: U2.54 (QSPI_SD2), U5.3 (~WP/IO_{2})
Q_IO3: U2.51 (QSPI_SD3), U5.7 (~HOLD/~RESET/IO_{3})
Q_SEL: R7.2, R9.2, U2.52 (QSPI_SCLK), U5.1 (~CS)
R0: U2.30 (GPIO19); also elsewhere on the board
R1: U2.31 (GPIO20); also elsewhere on the board
R2: U2.32 (GPIO21); also elsewhere on the board
R3: U2.34 (GPIO22); also elsewhere on the board
R4: U2.35 (GPIO23); also elsewhere on the board
R5: U2.36 (GPIO24); also elsewhere on the board
RGB: U2.4 (GPIO2), U8.2 (A)
SC0: J4.3, R49.1, U6.2 (SC0)
SC1: D166.1 (K), J5.3, R19.1, U6.4 (SC1)
SC2: D172.1 (K), J6.3, R44.1, U6.6 (SC2)
SC3: D173.1 (K), J7.3, R46.1, U6.8 (SC3)
SC4: D174.1 (K), J8.3, R50.1, U6.11 (SC4)
SC5: D163.1 (K), J3.3, R52.1, U6.13 (SC5)
SC6: D178.1 (K), J9.3, R54.1, U6.15 (SC6)
SCL: R17.2, U2.3 (GPIO1), U4.14 (SCL), U6.19 (SCL)
SD0: J4.2, R47.1, U6.1 (SD0)
SD1: D171.1 (K), J5.2, R18.1, U6.3 (SD1)
SD2: D175.1 (K), J6.2, R43.1, U6.5 (SD2)
SD3: D176.1 (K), J7.2, R45.1, U6.7 (SD3)
SD4: D177.1 (K), J8.2, R48.1, U6.10 (SD4)
SD5: D164.1 (K), J3.2, R51.1, U6.12 (SD5)
SD6: D179.1 (K), J9.2, R53.1, U6.14 (SD6)
SDA: R16.2, U2.2 (GPIO0), U4.15 (SDA), U6.20 (SDA)
SWC: J2.4, U2.24 (SWCLK)
SWD: J2.5, U2.25 (SWD)
XIN: C1.2, U2.20 (XIN), Y1.3
XOUT: C2.2, U2.21 (XOUT), Y1.1
~INT: U2.5 (GPIO3), U4.13 (~INT)
~RESET: J2.1, R6.2, RST1.2, U2.26 (RUN), U6.24 (~RESET)

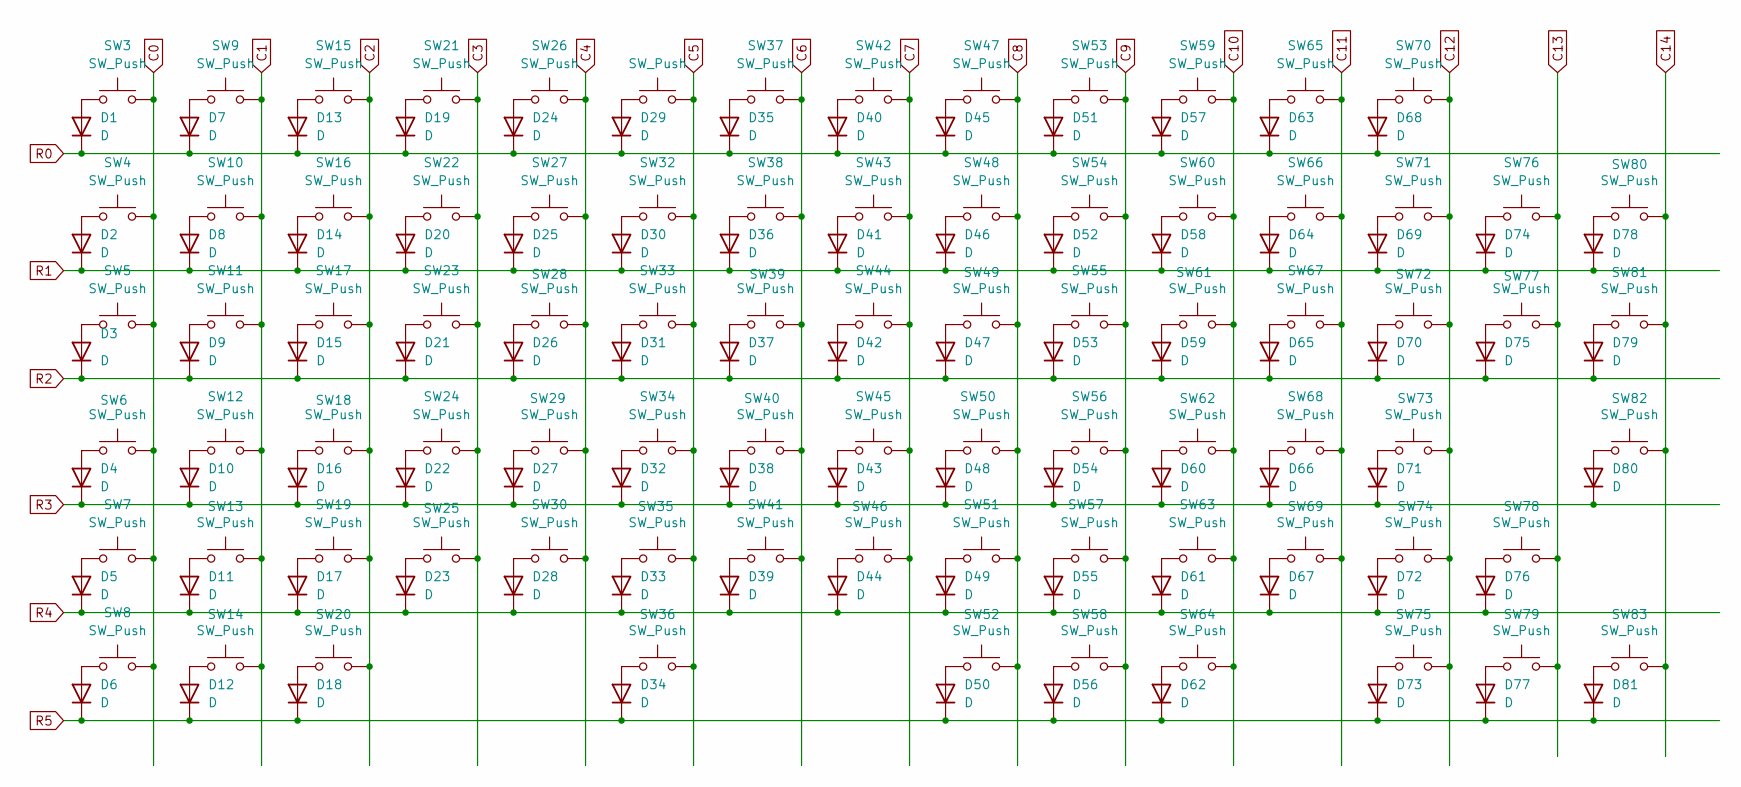
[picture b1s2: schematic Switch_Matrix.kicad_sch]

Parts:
D1, D2, D3, D4, D5, D6, D7, D8, D9, D10, D11, D12, D13, D14, D15, D16, D17, D18, D19, D20, D21, D22, D23, D24, D25, D26, D27, D28, D29, D30, D31, D32, D33, D34, D35, D36, D37, D38, D39, D40, D41, D42, D43, D44, D45, D46, D47, D48, D49, D50, D51, D52, D53, D54, D55, D56, D57, D58, D59, D60, D61, D62, D63, D64, D65, D66, D67, D68, D69, D70, D71, D72, D73, D74, D75, D76, D77, D78, D79, D80, D81: D; D_SOD-123
SW3, SW4, SW9, SW10, SW11, SW12, SW13, SW15, SW16, SW17, SW18, SW19, SW21, SW22, SW23, SW24, SW25, SW26, SW27, SW28, SW29, SW30, SW31, SW32, SW33, SW34, SW35, SW37, SW38, SW39, SW40, SW41, SW42, SW43, SW44, SW45, SW46, SW47, SW48, SW49, SW50, SW51, SW52, SW53, SW54, SW55, SW56, SW57, SW58, SW59, SW60, SW61, SW62, SW63, SW64, SW65, SW66, SW67, SW68, SW69, SW70, SW71, SW72, SW73, SW75, SW78, SW79, SW80, SW81, SW82, SW83: SW_Push; SW_Hotswap_Kailh_MX_1.00u
SW5: SW_Push; SW_Hotswap_Kailh_MX_1.50u
SW6, SW74: SW_Push; SW_Hotswap_Kailh_MX_1.75u
SW7, SW8, SW14, SW20: SW_Push; SW_Hotswap_Kailh_MX_1.25u
SW36: SW_Push; SW_Hotswap_Kailh_MX_6.25u
SW76: SW_Push; SW_Hotswap_Kailh_MX_2.00u
SW77: SW_Push; SW_Hotswap_Kailh_MX_ISOEnter

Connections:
C0: SW3.2, SW4.2, SW5.2, SW6.2, SW7.2, SW8.2; also elsewhere on the board
C1: SW9.2, SW10.2, SW11.2, SW12.2, SW13.2, SW14.2; also elsewhere on the board
C2: SW15.2, SW16.2, SW17.2, SW18.2, SW19.2, SW20.2; also elsewhere on the board
C3: SW21.2, SW22.2, SW23.2, SW24.2, SW25.2; also elsewhere on the board
C4: SW26.2, SW27.2, SW28.2, SW29.2, SW30.2; also elsewhere on the board
C5: SW31.2, SW32.2, SW33.2, SW34.2, SW35.2, SW36.2; also elsewhere on the board
C6: SW37.2, SW38.2, SW39.2, SW40.2, SW41.2; also elsewhere on the board
C7: SW42.2, SW43.2, SW44.2, SW45.2, SW46.2; also elsewhere on the board
C8: SW47.2, SW48.2, SW49.2, SW50.2, SW51.2, SW52.2; also elsewhere on the board
C9: SW53.2, SW54.2, SW55.2, SW56.2, SW57.2, SW58.2; also elsewhere on the board
C10: SW59.2, SW60.2, SW61.2, SW62.2, SW63.2, SW64.2; also elsewhere on the board
C11: SW65.2, SW66.2, SW67.2, SW68.2, SW69.2; also elsewhere on the board
C12: SW70.2, SW71.2, SW72.2, SW73.2, SW74.2, SW75.2; also elsewhere on the board
C13: SW76.2, SW77.2, SW78.2, SW79.2; also elsewhere on the board
C14: SW80.2, SW81.2, SW82.2, SW83.2; also elsewhere on the board
unnamed: D1.2 (A), SW3.1
unnamed: D2.2 (A), SW4.1
unnamed: D3.2 (A), SW5.1
unnamed: D4.2 (A), SW6.1
unnamed: D5.2 (A), SW7.1
unnamed: D6.2 (A), SW8.1
unnamed: D7.2 (A), SW9.1
unnamed: D8.2 (A), SW10.1
unnamed: D9.2 (A), SW11.1
unnamed: D10.2 (A), SW12.1
unnamed: D11.2 (A), SW13.1
unnamed: D12.2 (A), SW14.1
unnamed: D13.2 (A), SW15.1
unnamed: D14.2 (A), SW16.1
unnamed: D15.2 (A), SW17.1
unnamed: D16.2 (A), SW18.1
unnamed: D17.2 (A), SW19.1
unnamed: D18.2 (A), SW20.1
unnamed: D19.2 (A), SW21.1
unnamed: D20.2 (A), SW22.1
unnamed: D21.2 (A), SW23.1
unnamed: D22.2 (A), SW24.1
unnamed: D23.2 (A), SW25.1
unnamed: D24.2 (A), SW26.1
unnamed: D25.2 (A), SW27.1
unnamed: D26.2 (A), SW28.1
unnamed: D27.2 (A), SW29.1
unnamed: D28.2 (A), SW30.1
unnamed: D29.2 (A), SW31.1
unnamed: D30.2 (A), SW32.1
unnamed: D31.2 (A), SW33.1
unnamed: D32.2 (A), SW34.1
unnamed: D33.2 (A), SW35.1
unnamed: D34.2 (A), SW36.1
unnamed: D35.2 (A), SW37.1
unnamed: D36.2 (A), SW38.1
unnamed: D37.2 (A), SW39.1
unnamed: D38.2 (A), SW40.1
unnamed: D39.2 (A), SW41.1
unnamed: D40.2 (A), SW42.1
unnamed: D41.2 (A), SW43.1
unnamed: D42.2 (A), SW44.1
unnamed: D43.2 (A), SW45.1
unnamed: D44.2 (A), SW46.1
unnamed: D45.2 (A), SW47.1
unnamed: D46.2 (A), SW48.1
unnamed: D47.2 (A), SW49.1
unnamed: D48.2 (A), SW50.1
unnamed: D49.2 (A), SW51.1
unnamed: D50.2 (A), SW52.1
unnamed: D51.2 (A), SW53.1
unnamed: D52.2 (A), SW54.1
unnamed: D53.2 (A), SW55.1
unnamed: D54.2 (A), SW56.1
unnamed: D55.2 (A), SW57.1
unnamed: D56.2 (A), SW58.1
unnamed: D57.2 (A), SW59.1
unnamed: D58.2 (A), SW60.1
unnamed: D59.2 (A), SW61.1
unnamed: D60.2 (A), SW62.1
unnamed: D61.2 (A), SW63.1
unnamed: D62.2 (A), SW64.1
unnamed: D63.2 (A), SW65.1
unnamed: D64.2 (A), SW66.1
unnamed: D65.2 (A), SW67.1
unnamed: D66.2 (A), SW68.1
unnamed: D67.2 (A), SW69.1
unnamed: D68.2 (A), SW70.1
unnamed: D69.2 (A), SW71.1
unnamed: D70.2 (A), SW72.1
unnamed: D71.2 (A), SW73.1
unnamed: D72.2 (A), SW74.1
unnamed: D73.2 (A), SW75.1
unnamed: D74.2 (A), SW76.1
unnamed: D75.2 (A), SW77.1
unnamed: D76.2 (A), SW78.1
unnamed: D77.2 (A), SW79.1
unnamed: D78.2 (A), SW80.1
unnamed: D79.2 (A), SW81.1
unnamed: D80.2 (A), SW82.1
unnamed: D81.2 (A), SW83.1
R0: D1.1 (K), D7.1 (K), D13.1 (K), D19.1 (K), D24.1 (K), D29.1 (K), D35.1 (K), D40.1 (K), D45.1 (K), D51.1 (K), D57.1 (K), D63.1 (K), D68.1 (K); also elsewhere on the board
R1: D2.1 (K), D8.1 (K), D14.1 (K), D20.1 (K), D25.1 (K), D30.1 (K), D36.1 (K), D41.1 (K), D46.1 (K), D52.1 (K), D58.1 (K), D64.1 (K), D69.1 (K), D74.1 (K), D78.1 (K); also elsewhere on the board
R2: D3.1 (K), D9.1 (K), D15.1 (K), D21.1 (K), D26.1 (K), D31.1 (K), D37.1 (K), D42.1 (K), D47.1 (K), D53.1 (K), D59.1 (K), D65.1 (K), D70.1 (K), D75.1 (K), D79.1 (K); also elsewhere on the board
R3: D4.1 (K), D10.1 (K), D16.1 (K), D22.1 (K), D27.1 (K), D32.1 (K), D38.1 (K), D43.1 (K), D48.1 (K), D54.1 (K), D60.1 (K), D66.1 (K), D71.1 (K), D80.1 (K); also elsewhere on the board
R4: D5.1 (K), D11.1 (K), D17.1 (K), D23.1 (K), D28.1 (K), D33.1 (K), D39.1 (K), D44.1 (K), D49.1 (K), D55.1 (K), D61.1 (K), D67.1 (K), D72.1 (K), D76.1 (K); also elsewhere on the board
R5: D6.1 (K), D12.1 (K), D18.1 (K), D34.1 (K), D50.1 (K), D56.1 (K), D62.1 (K), D73.1 (K), D77.1 (K), D81.1 (K); also elsewhere on the board

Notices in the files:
README.md:
License:
PolyForm Noncommercial License 1.0.0 — see [LICENSE](LICENSE). Required notice:
Copyright (c) 2026 Neil Dalal.
